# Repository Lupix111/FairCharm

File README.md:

# FairCharm

A pocket camera that fits in your palm and can hang from your bag like a charm! It's fair because it's open-source and free for everyone. *The open camera you actually own.*

> [!NOTE]
> **Project status:** the PCB and the firmware are currently being tested on real hardware. Battery life, the power-cut behaviour and WiFi range are still to be verified, so take the numbers in this README as "expected", not "measured". I'll update everything as soon as I have real data!

**The people at PCBWay decided to help me out with the printed circuit board, shoutout to Aran and the fine people that work at [PCBWay](https://www.pcbway.com), they're providing me with a tight and clean PCB that will make this project free of any tangled and messed up wirenest. Go to PCBWay to get the PCB for the best price ever!**

Just an ESP32-CAM project that came to my mind when I saw a certain company make these pocket cameras with a 1.6 megapixel camera that are kinda trash and way too stupidly expensive.

## What can it do?

- Takes photos with the OV2640 sensor of the ESP32-CAM (up to UXGA, 1600x1200, so roughly 2 megapixels) and saves them as JPG on a microSD card.
- Beeps to tell you what's going on (ready, photo taken, error, going to sleep...). No screen needed!
- Creates its own WiFi network. Connect your phone, open a web page and swipe through your photos in a little carousel. No app, no cloud, no account.
- Can optionally send every photo to a **Telegram** chat or a **Discord** channel as soon as you take it.
- Can be updated over WiFi (**OTA**), so you don't need to unscrew it and plug cables every time there's a new firmware.
- Goes to sleep by itself when you're not using it to save battery.

## What you need

For this project you're gonna need a grand total of 9 pieces of hardware (not counting the wires):

- 1x **ESP32-CAM** (the AI-Thinker one with the OV2640 camera and PSRAM).
- 1x **Charging module with a boost converter to 5V**: the **CKCS PB0A** (USB-C, charges a single LiPo cell and boosts it to 5V). I initially planned to use a TP4056 but quickly found out that the ESP32-CAM needs 5V to function properly. [I now am the proud owner of 10 useless TP4056 modules]
- 1x **500mAh LiPo battery**, single cell (1S, 3.7V). The small flat ones like the 502035 or 503035 sizes are perfect.
- 1x **Big red button** (or any colour really), the 12x12mm clicky ones. This is the shutter!
- 1x **SMD Passive buzzer, MTP-5020**, it has to be *passive*, an active one has its own oscillator and won't play the different beeps. 
- 1x **microSD card**, formatted as FAT32. The ESP32-CAM datasheet officially says up to 4GB, bigger cards usually work too but test yours before trusting it.
- 1x **FairCharm PCB** (optional but highly suggested, it's much easier to use the PCB than doing it by hand).
- 1x **small 6x6 tactile switch** for the power button. 
- 1x **SMD or THT Capacitor, 10v 330uF, 6.3x5.4**.
- You'll also need some **3D printed parts** so you're either gonna have to buy them OR ask a friend that got a printer.

There's also a **template to customize the back and the front** of the camera, you just need GIMP and some sort of idea on what to put there, after that it's only scissors, glue and...voilà! And there's the **STL files** for the body of the camera. 

> [!WARNING]
> **Charging safety, please read!** The PB0A charges at up to **2.1A** by default. That is a LOT for a 500mAh pouch cell (small LiPos like these are usually charged at around 0.3C to 1C, so roughly 150 to 500mA). The module can only lower that limit through its I2C interface, which this project doesn't use (yet). Until that's solved, please measure the real charging current with a USB power meter on your first charge, don't charge it unattended, and stop immediately if the battery gets warm or puffy. If you want a worry-free setup, use a bigger battery or a cell that is rated for fast charging.

## Using it

1. Put the microSD card in the ESP32-CAM.
2. Press the **power button** (the one on the K pin of the charging module). The module has no on/off switch, that's the button that turns the 5V on.
3. Wait for **2 short beeps**. That's the "I'm ready let's go" signal.
4. Press the **big red button** to take a photo. You'll hear 2 rising beeps when it's saved.
5. Done! The photos are on the SD card as 'photo_00001.jpg', 'photo_00002.jpg', and so on. The counter keeps going even after a reboot, so old photos never get overwritten.

The small flash LED on the ESP32-CAM stays **dimly lit** while the camera is on, it's on purpose: it's the "yes, I'm awake" light (it shares a pin with the shutter button).

### What do the beeps mean?

| Sound | Meaning |
|-------|---------|
| 2 short beeps | Ready to shoot |
| 2 rising beeps | Photo saved |
| 1 short high beep (after a photo) | Photo uploaded to Telegram / Discord |
| 1 long low beep (after a photo) | Upload failed (the photo is still safe on the SD card) |
| 2 low beeps | Error: the camera or the SD card didn't start, or the photo couldn't be saved |
| 3 falling beeps | Going to sleep |

### Sleeping and waking up

After **60 seconds** without doing anything the camera goes into deep sleep. About 30 seconds later the charging module notices that almost no current is being used and cuts the 5V completely (that's its default behaviour, and it's actually great for the battery).

- Press the **big red button** to wake it up (works while it's still in deep sleep, so in the first ~30 seconds, or when it's plugged into USB-C).
- If the power was cut, press the **power button** on the charging module to turn it on again.

If your phone is connected to the camera's WiFi the sleep timer is 5 minutes instead of 1, so you have time to browse your photos or update the firmware.
(but you can totally change this and give yourself more time)

### Seeing your photos on your phone

1. Connect to the WiFi network called **'ESP32-CAM'**. The default password is **'12345678'**. Please change it, it's in the firmware ('ap_ssid' and 'ap_password')!
2. Open **http://192.168.4.1** in your browser.
3. You'll see the carousel: newest photo first, ◀ goes to the older one and ▶ to the newer one. You can also use the arrow keys on a computer or swipe on a phone. The **Download** button saves the current photo.

The ESP32 is a tiny chip, so photos take around 1 to 3 seconds to load. Be patient with it, it's doing its best!

## Building it

### With the PCB (the easy way)

Solder the parts to the PCB, plug in the ESP32-CAM, solder the battery wires to the battery pads of the charging module and you're done. No wirenest.

> [!WARNING]
> The CKCS PB0A has **no reverse polarity protection**. If you connect the battery the wrong way, the module is dead, dead-dead-dead. The battery symbol on the module has a tiny "pin": that's the **positive** terminal (BAT+). Check your battery wires with a multimeter, cheap LiPos often come with the red and black wires the other way around from what you'd expect!

### By hand (the hard way)

If you really wanna do it by hand, this is how everything connects:

| From | To |
|------|----|
| PB0A 'OUT+' | ESP32-CAM '5V' |
| PB0A 'OUT-' | ESP32-CAM 'GND' |
| Battery '+' / '-' | PB0A battery pads (mind the polarity!) |
| PB0A 'K' | 10kΩ resistor, then the power button, then 'GND' |
| Shutter button | ESP32-CAM 'IO4' and 'GND' |
| Buzzer | ESP32-CAM 'IO12', through a 330Ω resistor, to 'GND' |

For the buzzer, put a small diode (like a 1N4007 or a 1N4148) in parallel to it, with the stripe (cathode) on the side of the pin. It protects the pin from voltage spikes. Also put a bulk capacitor (something like 220uF) between 5V and GND, close to the ESP32-CAM. When you unplug the USB-C cable the charging module has a tiny power gap that can reboot the camera, the capacitor smooths it out.

**Don't connect the shutter button and the power button together!** The charging module reads two quick presses on its button as "turn off", so they have to be two separate buttons.

### Pin map

| Function | ESP32-CAM pin | Notes |
|----------|---------------|-------|
| Shutter button | GPIO4 (to GND) | Internal pull-up. It's also the flash LED line |
| Buzzer | GPIO12 | Boot pin: it must be LOW when the chip starts, the buzzer to GND takes care of it |
| SD card | 1-bit mode | Frees GPIO4, 12 and 13 (writing speed is a bit lower, still plenty for photos) |
| Power button | 'K' pin of the PB0A | With a 10kΩ resistor in series |
| Programming header (J1) | IO0, GND, TX, RX | Only needed to flash the firmware the first time |
| Not used | GPIO13, GPIO16 | **Don't touch GPIO16**, it's wired to the PSRAM |

## Flashing the firmware

### 1. Set up the Arduino IDE

Install the **ESP32 boards package** (by Espressif Systems) in the Arduino IDE. You don't need any extra library, everything the firmware uses comes with it.

Then use these settings:

| Setting | Value |
|---------|-------|
| Board | AI Thinker ESP32-CAM |
| CPU Frequency | 240MHz (WiFi/BT) |
| Flash Mode | QIO |
| Flash Frequency | 80MHz |
| **Partition Scheme** | **Minimal SPIFFS (1.9MB APP with OTA/128KB SPIFFS)** |
| Upload Speed | 115200 |

The partition scheme is the important one, VERY IMPORTANT! With the default "Huge APP" there's no room for OTA updates.

### 2. Create your 'secrets.h' (optional)

Copy 'secrets.example.h' to 'secrets.h' (same folder as 'test_cam.ino') and fill in what you need. Everything is optional: without 'secrets.h' the camera works fine, it just won't have OTA, Telegram or Discord. An empty field means "feature off".

### 3. First upload (with a cable)

The very first time you need a cable, after that you can use OTA.

- **Easiest:** flash the ESP32-CAM *before* putting it on the PCB, using its dedicated programmer board (the ESP32-CAM-MB).
- **On the PCB:** use the programming header 'J1' with a USB-serial adapter (3.3V logic). Connect 'GND', 'TX' and 'RX' (TX to the adapter's RX and the other way around), put a jumper between 'IO0' and 'GND', and turn the camera on with the power button. Upload the sketch, then remove the jumper and power-cycle the camera. **Don't connect the adapter's 5V pin**, the camera is powered by the battery.

### 4. Updating over WiFi (OTA)

Set an 'OTA_PASSWORD' in 'secrets.h'. Without a password OTA stays off on purpose: the default WiFi password is public, so otherwise anyone nearby could flash your camera!

Then you have two ways:

- **Arduino IDE:** connect your computer to the 'ESP32-CAM' network, pick the network port 'esp32-cam' and upload as usual. It will ask for your OTA password.
- **Web page (works from a phone too):** export the binary ('Sketch > Export Compiled Binary'), open **http://192.168.4.1/update**, log in with the user 'admin' and your OTA password, pick the '.bin' and press the button.

> [!CAUTION]
> Don't update with a nearly empty battery, and don't flash a firmware that breaks the WiFi: you'd lose OTA and you'd need the cable again. That's why the 'J1' programming header exists!

## Telegram and Discord

The camera has to join a WiFi network with internet (your home router or your phone's hotspot) to send the photos. Put its name and password in 'secrets.h' ('STA_SSID' and 'STA_PASSWORD'). The camera's own network stays on, so you can still browse your photos.

### Telegram

1. On Telegram, talk to **@BotFather**, send '/newbot' and follow the steps. It will give you a **token**.
2. Open a chat with your new bot and send it any message (like '/start').
3. Open 'https://api.telegram.org/bot<YOUR_TOKEN>/getUpdates' in a browser and look for '"chat":{"id":...}'. That number is your **chat id**.
4. Put the token and the chat id in 'secrets.h' ('TELEGRAM_BOT_TOKEN' and 'TELEGRAM_CHAT_ID').

Telegram recompresses normal photos. If you want the original file, set 'TELEGRAM_AS_DOCUMENT' to 'true' in the firmware.

### Discord

1. In your Discord server go to the channel settings, then **Integrations**, then **Webhooks** and create a new one.
2. Copy the **webhook URL** and put it in 'secrets.h' ('DISCORD_WEBHOOK_URL').

### How it behaves

Every photo is uploaded in the background, so you can keep shooting while the previous one is being sent. You'll hear a high beep when it's done or a low one if it failed. If the camera can't find your WiFi (say you're out and about) it tries for about 15 seconds, then gives up. Your photo is always saved on the SD card first.

## Known limitations

- **No security checks on the cloud connection:** the camera encrypts the connection to Telegram and Discord but doesn't verify the server's certificate. For a hobby camera that's fine, but don't use it for anything sensitive.
- **Photos taken offline aren't sent later:** they stay on the SD card and you get them from the carousel.
- **The web server is small:** it serves one thing at a time, so sometimes a page takes a few seconds, and the shutter button doesn't react while a photo is being sent to your phone.
- **WiFi range:** the antenna is a PCB trace and it doesn't like metal or copper nearby (the battery included). Range is still to be measured on the real hardware.
- **Photos on the carousel:** only '.jpg' files with simple names (letters, numbers, '_', '-', '.' and spaces) show up.
- **Charging current:** see the safety note above.

## Ideas for later

- Video recording (AVI / Motion JPEG).
- Thumbnails in the carousel, to make browsing faster.
- Limiting the battery charging current properly.
- Sending the photos that were taken offline as soon as the WiFi is back.

Got another idea? Open an issue!

## Troubleshooting

Open the Arduino IDE **Serial Monitor at 115200 baud** and look at what the camera says.

- 'Camera init failed': check that the camera ribbon cable is fully inserted, and that the power is good (5V).
- 'SD mount failed': the card has to be FAT32 and well seated. Try another card.
- Upload doesn't work: after taking a photo, look for 'Server response:' in the Serial Monitor. A '200' (Telegram) or '204' (Discord) means it worked. Anything else comes with a short error from the server, like "chat not found" if the chat id is wrong.
- The camera reboots when you unplug USB-C: add the bulk capacitor (see "By hand").

## Contributing

Pull requests, issues and weird ideas are all welcome! This is an open project, so if you build one, make it better, or break it in an interesting way, tell me about it.

## Author

Made by [@Lupix111](https://github.com/Lupix111).

## Thanks to

- **Aran and the people at [PCBWay](https://www.pcbway.com)** for sponsoring the PCB.
- The write-up about the [CKCS PB0A module on done.land](https://done.land/components/power/powersupplies/battery/chargers/charge-discharge/ip5306/pb0a/), which explained everything the module's seller forgot to.

Now go and take some photos.

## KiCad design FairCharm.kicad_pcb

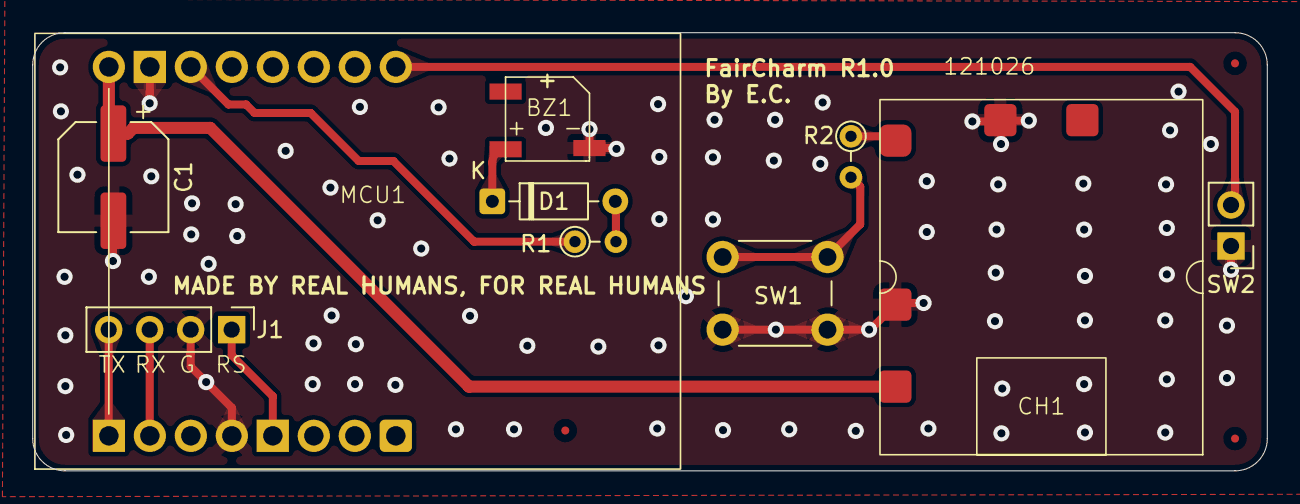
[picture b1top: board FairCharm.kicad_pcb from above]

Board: 2 copper layers, 76.5 x 27.2 mm, 13 parts (0 on the bottom side), 11 nets.

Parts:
BZ1: Buzzer; MLT-5020
C1: C_Pol 330u; CP_Elec_6.3x5.4_Nichicon
CH1: CKCS PB0A
D1: D; D_DO-35_SOD27_P7.62mm_Horizontal
FID1, FID2, FID3: Fiducial; Fiducial_0.5mm_Mask1.5mm
J1: Conn_01x04_Pin; PinHeader_1x04_P2.54mm_Vertical
MCU1: ESP32-CAM AI THINKER; test-esp32-cam
R1: 100-330; R_Axial_DIN0204_L3.6mm_D1.6mm_P2.54mm_Vertical
R2: 10K; R_Axial_DIN0204_L3.6mm_D1.6mm_P2.54mm_Vertical
SW1: SW_Push; SW_PUSH_6mm
SW2: SW_Push Shutter; PinHeader_1x02_P2.54mm_Vertical

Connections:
GND: BZ1.2 (-), C1.2, CH1.2 (BAT-), CH1.4 (OUT-), J1.2, MCU1.2 (GND), MCU1.13 (GND), SW1.2, SW2.1
unnamed: BZ1.1 (+), D1.1 (K)
unnamed: CH1.5 (K), R2.1
unnamed: C1.1, CH1.3 (OUT+), MCU1.1 (5V)
unnamed: D1.2 (A), R1.2
unnamed: J1.1, MCU1.14 (IO0)
unnamed: J1.3, MCU1.11 (U0RXD)
unnamed: J1.4, MCU1.10 (U0TXD)
unnamed: MCU1.8 (IO4), SW2.2
unnamed: MCU1.3 (IO12), R1.1
unnamed: R2.2, SW1.1

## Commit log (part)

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2026-04-13 Add files via upload
    the first iteration of this design that I'm confident enough to post. There's also a GIMP template to help you further personalize the front and back of your very own FairCharm.
2026-05-15 Add files via upload
    added hole for buzzer and made the usb-c port larger
2026-05-15 Update README.md
    buzzer update
